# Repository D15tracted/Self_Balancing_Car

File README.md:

# Self_Balancing_Car
This is a project based on tutorials from Bilibili, it have different mechanical stucture and controw board, it use a dm3519 brushless motor instead of a brush motor

related libaries: https://jiangxiekeji.com/download.html
                  https://gitee.com/kit-miao/damiao

Updates:
2026/3/10 implement HAL library

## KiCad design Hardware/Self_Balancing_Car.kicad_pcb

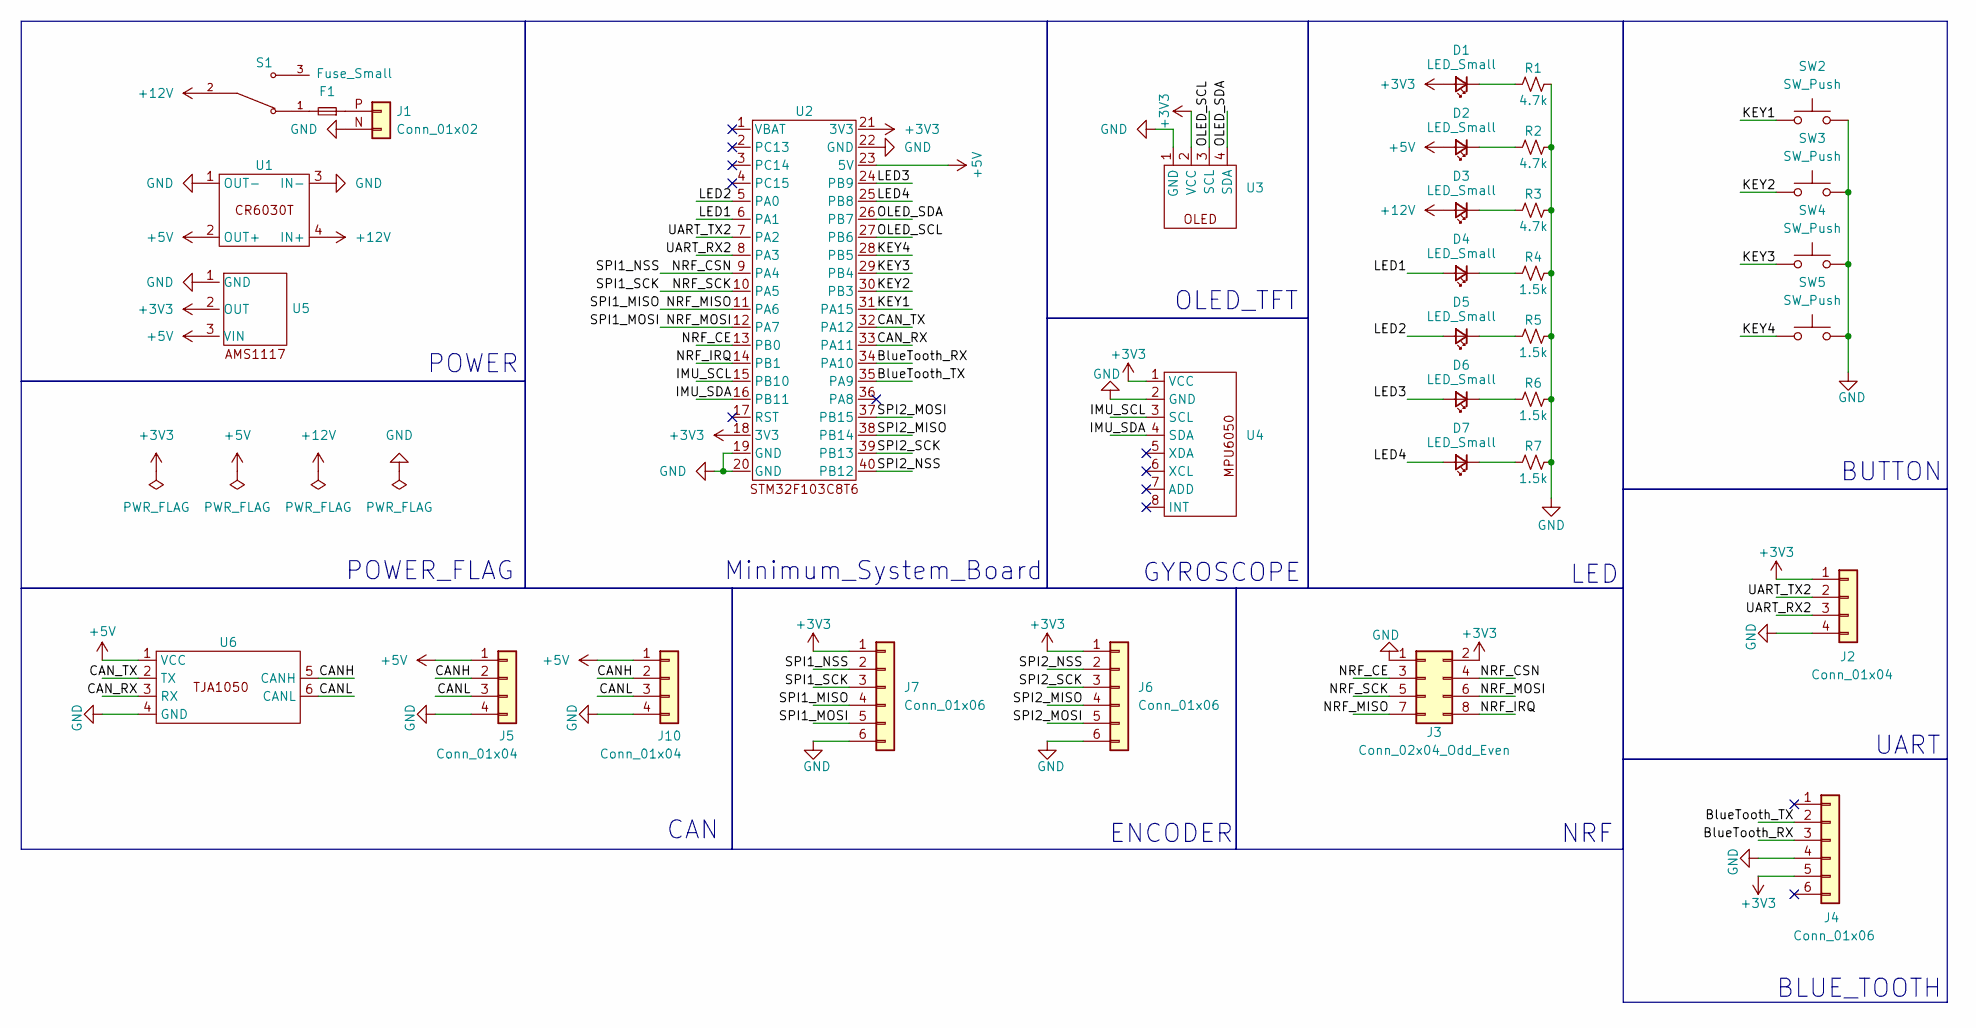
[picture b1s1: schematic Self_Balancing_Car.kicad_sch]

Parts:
D1, D2, D3, D4, D5, D6, D7: LED_Small; LED_0805_2012Metric
F1: Fuse_Small; Fuse_Blade_ATO_directSolder
J1: Conn_01x02; AMASS_XT60-M
J2, J5, J10: Conn_01x04; JST_PH_B4B-PH-K_1x04_P2.00mm_Vertical
J3: Conn_02x04_Odd_Even; NRF24L01
J4: Conn_01x06; BLUE_TOOTH
J6, J7: Conn_01x06; JST_PH_B6B-PH-K_1x06_P2.00mm_Vertical
R1, R2, R3: 4.7k; R_0805_2012Metric
R4, R5, R6, R7: 1.5k; R_0805_2012Metric
S1: SS12D10
SW2, SW3, SW4, SW5: SW_Push; KEY6x6
U1: CR6030T
U2: STM32F103C8T6_Minimum_System_Board
U3: OLED
U4: MPU6050
U5: AMS1117_Vertical
U6: TJA1050

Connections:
+3V3: D1.2 (A), J2.1, J3.2, J4.5, J6.1, J7.1, U2.18 (3V3), U2.21 (3V3), U3.2 (VCC), U4.1 (VCC), U5.2 (OUT)
+5V: D2.2 (A), J5.1, J10.1, U1.2 (OUT+), U2.23 (5V), U5.3 (VIN), U6.1 (VCC)
+12V: D3.2 (A), S1.2, U1.4 (IN+)
/BlueTooth_RX: J4.3, U2.34 (PA10)
/BlueTooth_TX: J4.2, U2.35 (PA9)
/CANH: J5.2, J10.2, U6.5 (CANH)
/CANL: J5.3, J10.3, U6.6 (CANL)
/CAN_RX: U2.33 (PA11), U6.3 (RX)
/CAN_TX: U2.32 (PA12), U6.2 (TX)
/IMU_SCL: U2.15 (PB10), U4.3 (SCL)
/IMU_SDA: U2.16 (PB11), U4.4 (SDA)
/KEY1: SW2.1, U2.31 (PA15)
/KEY2: SW3.1, U2.30 (PB3)
/KEY3: SW4.1, U2.29 (PB4)
/KEY4: SW5.1, U2.28 (PB5)
/LED1: D4.2 (A), U2.6 (PA1)
/LED2: D5.2 (A), U2.5 (PA0)
/LED3: D6.2 (A), U2.24 (PB9)
/LED4: D7.2 (A), U2.25 (PB8)
/NRF_CE: J3.3, U2.13 (PB0)
/NRF_CSN: J3.4, J7.2, U2.9 (PA4)
/NRF_IRQ: J3.8, U2.14 (PB1)
/NRF_MISO: J3.7, J7.4, U2.11 (PA6)
/NRF_MOSI: J3.6, J7.5, U2.12 (PA7)
/NRF_SCK: J3.5, J7.3, U2.10 (PA5)
/OLED_SCL: U2.27 (PB6), U3.3 (SCL)
/OLED_SDA: U2.26 (PB7), U3.4 (SDA)
/SPI2_MISO: J6.4, U2.38 (PB14)
/SPI2_MOSI: J6.5, U2.37 (PB15)
/SPI2_NSS: J6.2, U2.40 (PB12)
/SPI2_SCK: J6.3, U2.39 (PB13)
/UART_RX2: J2.3, U2.8 (PA3)
/UART_TX2: J2.2, U2.7 (PA2)
GND: J1.N (Pin_2), J2.4, J3.1, J4.4, J5.4, J6.6, J7.6, J10.4, R1.2, R2.2, R3.2, R4.2, R5.2, R6.2, R7.2, SW2.2, SW3.2, SW4.2, SW5.2, U1.1 (OUT-), U1.3 (IN-), U2.19 (GND), U2.20 (GND), U2.22 (GND), U3.1 (GND), U4.2 (GND), U5.1 (GND), U6.4 (GND)
unnamed: D1.1 (K), R1.1
unnamed: D2.1 (K), R2.1
unnamed: D3.1 (K), R3.1
unnamed: D4.1 (K), R4.1
unnamed: D5.1 (K), R5.1
unnamed: D6.1 (K), R6.1
unnamed: D7.1 (K), R7.1
unnamed: F1.2, S1.1
unnamed: F1.1, J1.P (Pin_1)

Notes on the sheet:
BUTTON
Minimum_System_Board
LED
ENCODER
POWER
NRF
GYROSCOPE
UART
POWER_FLAG
OLED_TFT
CAN
BLUE_TOOTH

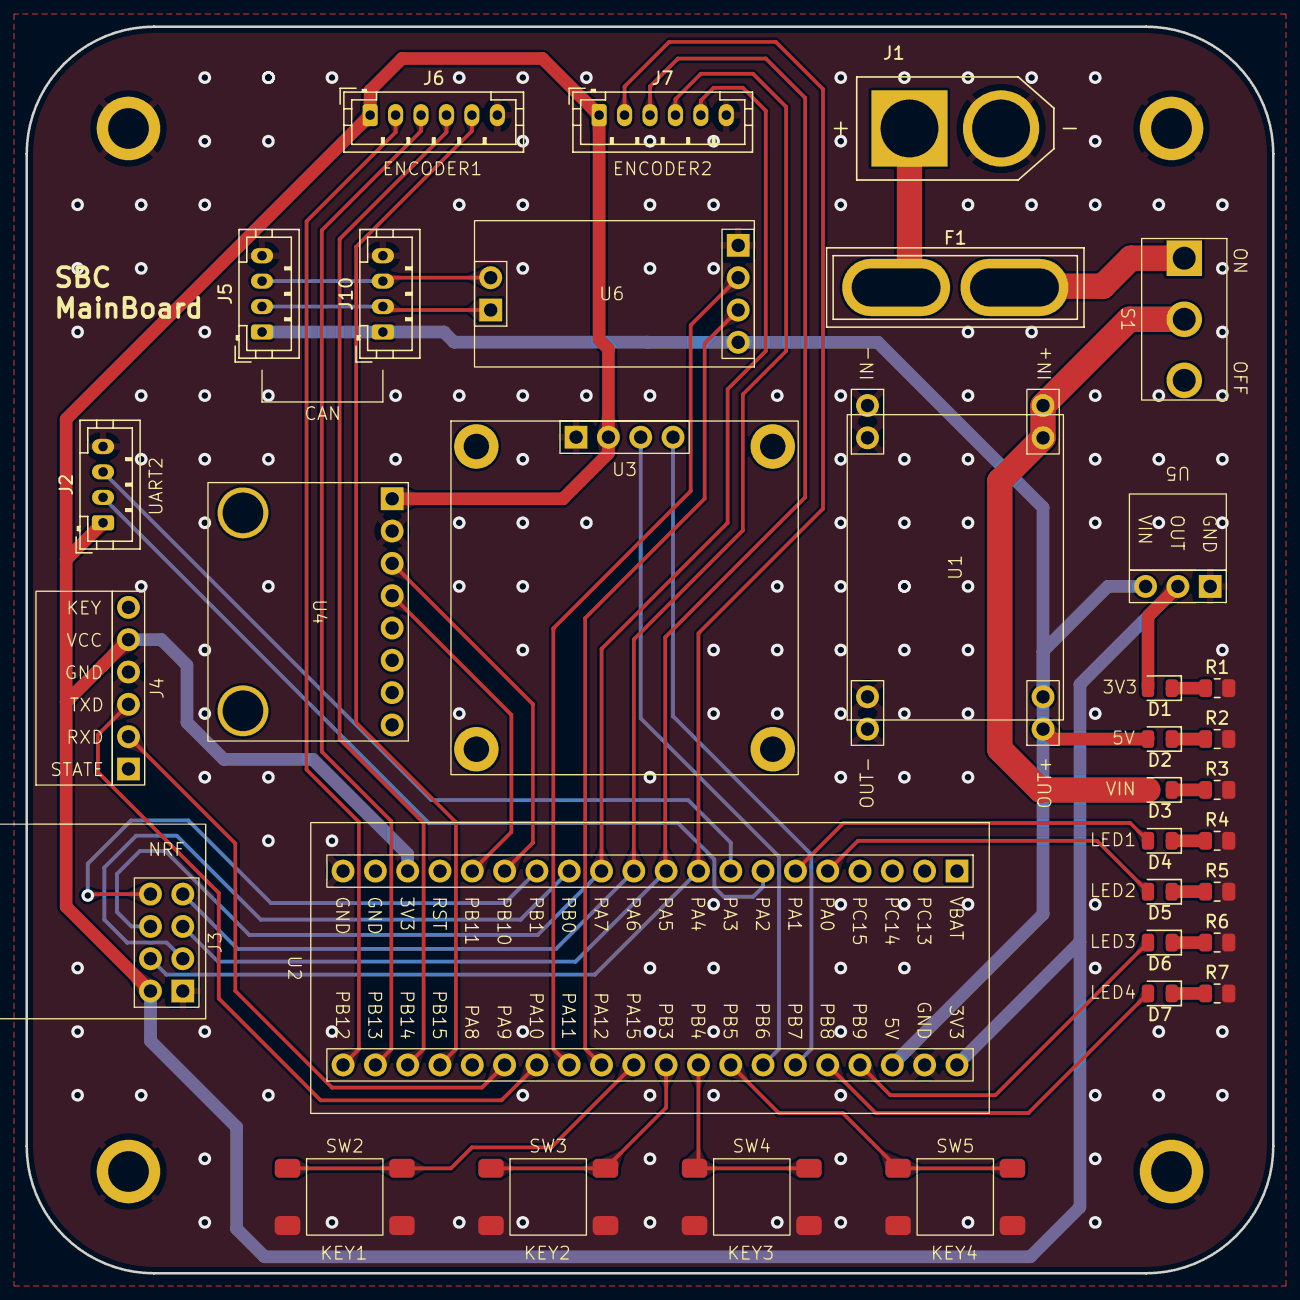
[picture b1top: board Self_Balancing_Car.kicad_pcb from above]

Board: 2 copper layers, 98.0 x 98.0 mm, 34 parts (0 on the bottom side), 43 nets.

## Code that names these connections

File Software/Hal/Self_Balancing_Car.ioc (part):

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Mcu.Name=STM32F103C(8-B)Tx
Mcu.Package=LQFP48
Mcu.UserName=STM32F103C8Tx
PA0-WKUP.GPIOParameters=GPIO_Label
PA0-WKUP.GPIO_Label=LED2
PA0-WKUP.Signal=GPIO_Output
PA1.GPIOParameters=GPIO_Label
PA1.GPIO_Label=LED1
PA1.Signal=GPIO_Output
PA10.GPIOParameters=GPIO_PuPd
PA10.GPIO_PuPd=GPIO_PULLUP
PA10.Mode=Asynchronous
PA10.Signal=USART1_RX
PA11.Mode=CAN_Activate
PA11.Signal=CAN_RX
PA12.Mode=CAN_Activate
PA12.Signal=CAN_TX
PA13.Mode=Serial_Wire
PA13.Signal=SYS_JTMS-SWDIO
PA14.Mode=Serial_Wire
PA14.Signal=SYS_JTCK-SWCLK
PA15.GPIOParameters=GPIO_PuPd,GPIO_Label
PA15.GPIO_Label=KEY1
PA15.GPIO_PuPd=GPIO_PULLUP
PA15.Signal=GPIO_Input
PA9.Mode=Asynchronous
PA9.Signal=USART1_TX
PB10.GPIOParameters=GPIO_Speed,GPIO_PuPd,GPIO_ModeDefaultOutputPP
PB10.GPIO_ModeDefaultOutputPP=GPIO_MODE_OUTPUT_OD
PB10.GPIO_PuPd=GPIO_NOPULL
PB10.GPIO_Speed=GPIO_SPEED_FREQ_HIGH
PB10.Signal=GPIO_Output
PB11.GPIOParameters=GPIO_Speed,GPIO_PuPd,GPIO_ModeDefaultOutputPP
PB11.GPIO_ModeDefaultOutputPP=GPIO_MODE_OUTPUT_OD
PB11.GPIO_PuPd=GPIO_NOPULL
PB11.GPIO_Speed=GPIO_SPEED_FREQ_HIGH
PB11.Signal=GPIO_Output
PB3.GPIOParameters=GPIO_PuPd,GPIO_Label
PB3.GPIO_Label=KEY2
PB3.GPIO_PuPd=GPIO_PULLUP
PB3.Signal=GPIO_Input
PB4.GPIOParameters=GPIO_PuPd,GPIO_Label
PB4.GPIO_Label=KEY3
PB4.GPIO_PuPd=GPIO_PULLUP
PB4.Signal=GPIO_Input
PB5.GPIOParameters=GPIO_PuPd,GPIO_Label
PB5.GPIO_Label=KEY4
PB5.GPIO_PuPd=GPIO_PULLUP
PB5.Signal=GPIO_Input
PB6.GPIOParameters=GPIO_Speed,GPIO_PuPd,GPIO_ModeDefaultOutputPP
PB6.GPIO_ModeDefaultOutputPP=GPIO_MODE_OUTPUT_OD
PB6.GPIO_PuPd=GPIO_NOPULL
PB6.GPIO_Speed=GPIO_SPEED_FREQ_HIGH
PB6.Signal=GPIO_Output
PB7.GPIOParameters=GPIO_Speed,GPIO_PuPd,GPIO_ModeDefaultOutputPP
PB7.GPIO_ModeDefaultOutputPP=GPIO_MODE_OUTPUT_OD
PB7.GPIO_PuPd=GPIO_NOPULL
PB7.GPIO_Speed=GPIO_SPEED_FREQ_HIGH
PB7.Signal=GPIO_Output
PB8.GPIOParameters=GPIO_Label
PB8.GPIO_Label=LED4
PB8.Signal=GPIO_Output
PB9.GPIOParameters=GPIO_Label
PB9.GPIO_Label=LED3
PB9.Signal=GPIO_Output
PC14-OSC32_IN.Mode=LSE-External-Oscillator
PC14-OSC32_IN.Signal=RCC_OSC32_IN
PC15-OSC32_OUT.Mode=LSE-External-Oscillator
PC15-OSC32_OUT.Signal=RCC_OSC32_OUT
PD0-OSC_IN.Mode=HSE-External-Oscillator
PD0-OSC_IN.Signal=RCC_OSC_IN
PD1-OSC_OUT.Mode=HSE-External-Oscillator
PD1-OSC_OUT.Signal=RCC_OSC_OUT
RCC.SYSCLKFreq_VALUE=72000000
RCC.SYSCLKSource=RCC_SYSCLKSOURCE_PLLCLK
board=custom

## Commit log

2026-02-21 Update README with project details and resources
    Added project description and related libraries links.
2026-02-21 Add related libraries links to README
    Added links to related libraries for project resources.
2026-03-03 HAL implement
2026-03-03 Add updates section to README
    Added updates section with HAL library implementation date.
